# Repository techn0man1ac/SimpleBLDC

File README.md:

# SimpleBLDC

This is simple Arduino based 650W BLDC motor(with Hall sensors) controller. Designed with [KiCAD](https://www.kicad.org/). This controller has version V0.1, which means it is still under development. In addition, the project supports Field-Oriented Control (FOC), which is implemented using the [SimpleFOC library](https://github.com/simplefoc). 

All of this together enables a wide range of functions, such as precise rotor positioning (servo mode), phase current control, speed control, and much, much more. **Source code files (HW or SW) may change over time.**

Simple BLDC 3-Phase BLDC motor driver specs:
- Battery: 8S 
- VCC: 24.0V to 33.6V
- I(max): 20A 
- Сurrent measurements per phase

The device has the following features:
- XT60 power connector;
- Arduino Nano V3.0 main controller;
- Overcurrent protection (fuse);
- Reverse polarity protection;
- The ability to work with non-collector motors via Hall sensors (electric scooter or electric bicycle);
- Monitoring and control of the current of each phase (current is measured in both positive and negative directions);
- Current control by PWM, operating frequency 16/32 kHz;
- Has a connector for connecting a traction control potentiometer and a reverse button.
- Publication of the project under the [MIT license](https://github.com/techn0man1ac/SimpleBLDC/blob/main/LICENSE).

# Schematic

The device has 3 drivers for mosfet transistors, as well as 3 current sensors based on the Hall effect, which measure both in the positive and negative directions. The use of 3 sensors is the reason for the development of the device for regenerative braking.

# PCB

The board consists of two layers: top and bottom. All the main parts are located on the top layer.

The bottom layer contains mainly earth and power tracks.

Board sizes is 72 x 99 mm:

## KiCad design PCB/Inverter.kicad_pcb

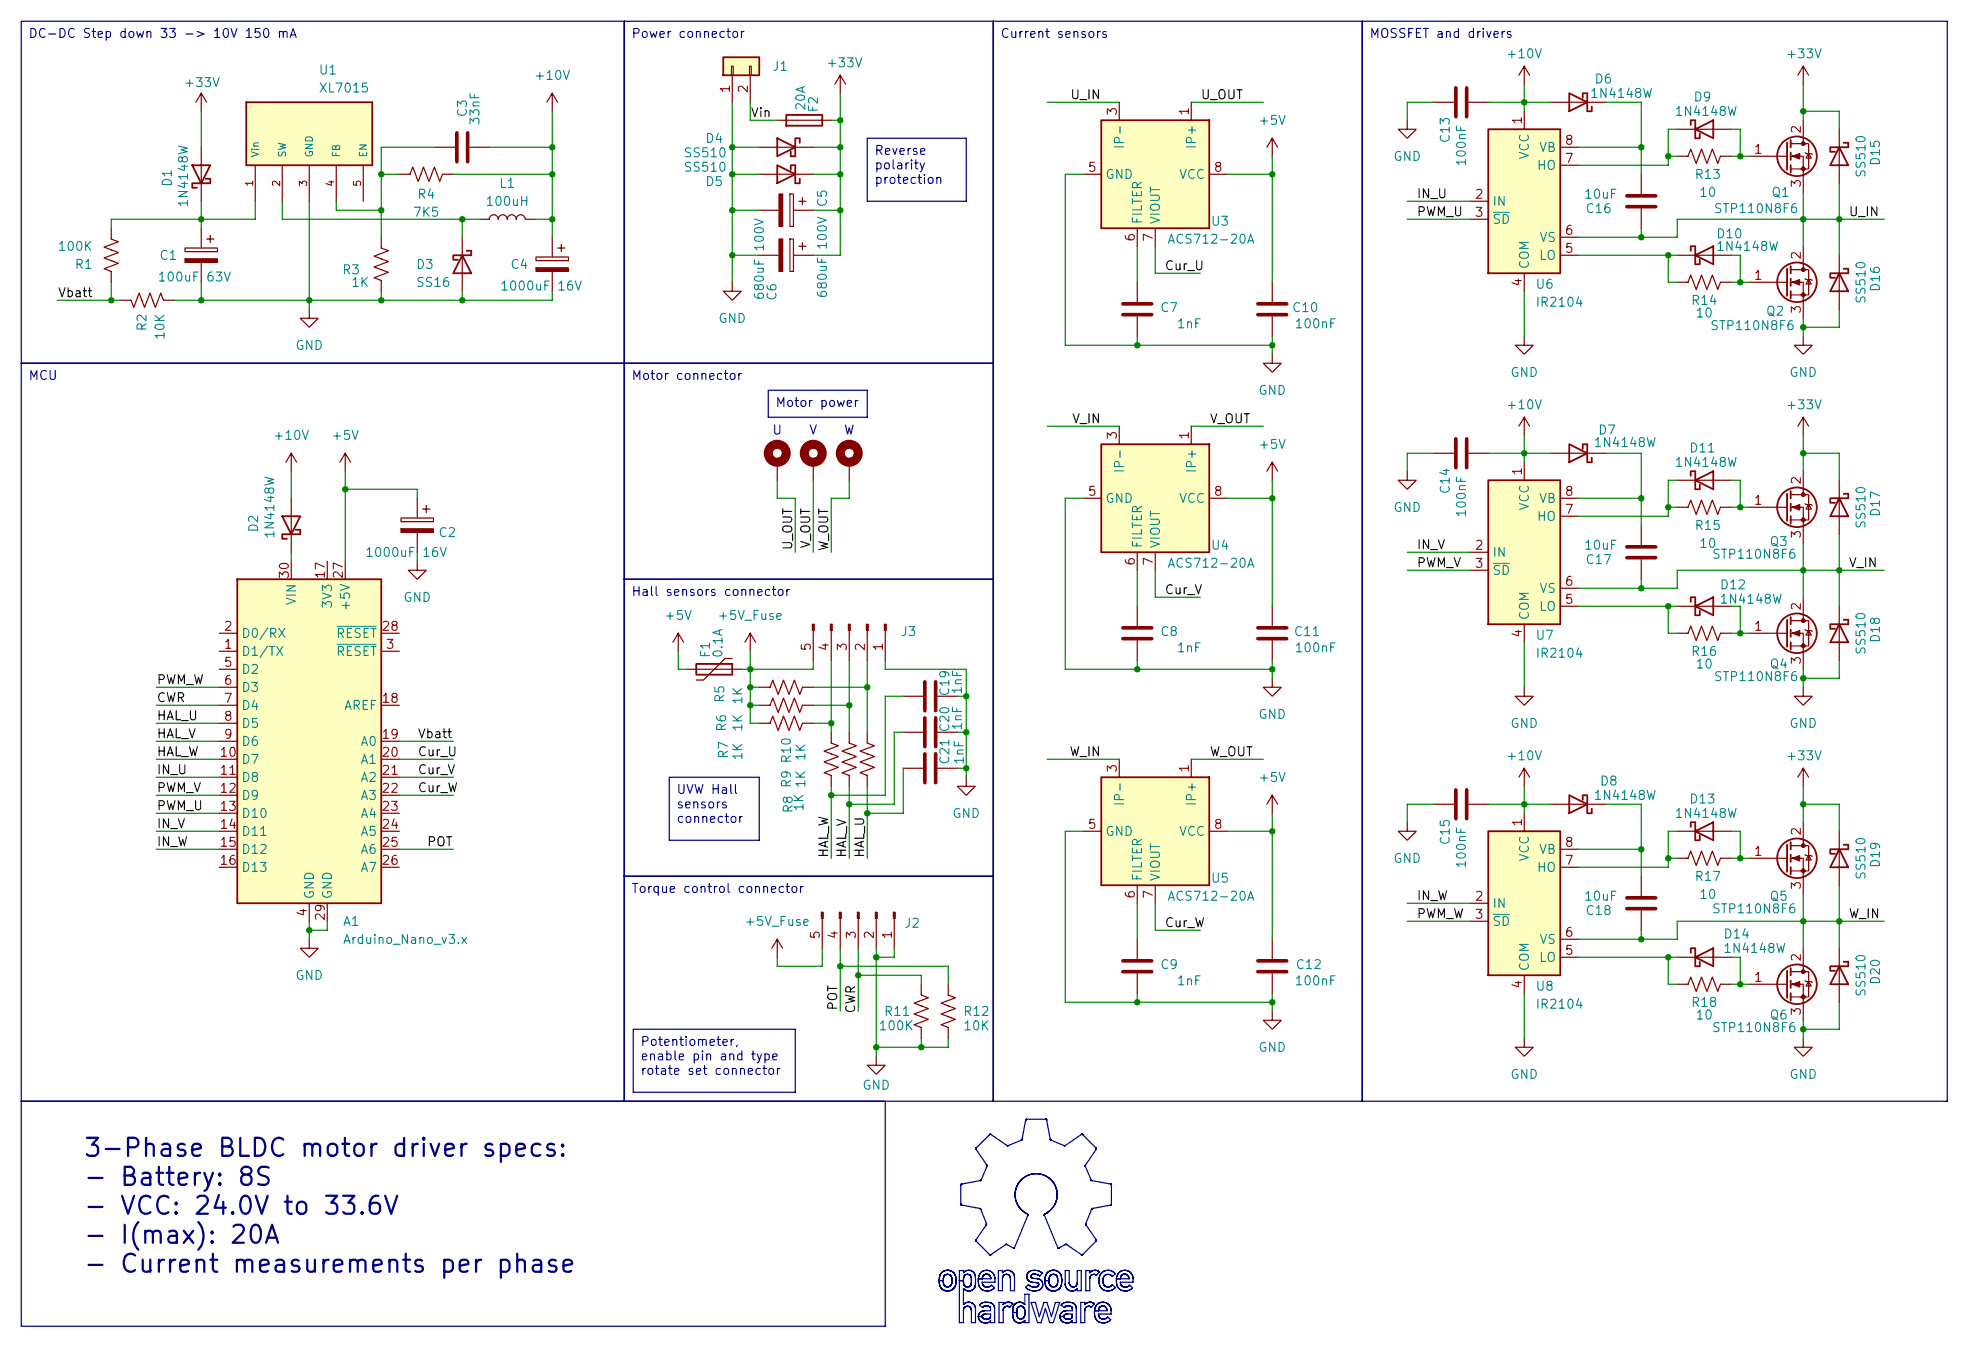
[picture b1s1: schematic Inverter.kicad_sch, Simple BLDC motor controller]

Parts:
A1: Arduino_Nano_v3.x; Arduino_Nano
C1: 100uF 63V; CP_Elec_10x10.5
C2, C4: 1000uF 16V; CP_Elec_10x10.5
C3: 33nF; C_0805_2012Metric_Pad1.18x1.45mm_HandSolder
C5, C6: 680uF 100V; CP_Radial_D16.0mm_P7.50mm
C7, C8, C9, C19, C20, C21: 1nF; C_0805_2012Metric_Pad1.18x1.45mm_HandSolder
C10, C11, C12, C13, C14, C15: 100nF; C_0805_2012Metric_Pad1.18x1.45mm_HandSolder
C16, C17, C18: 10uF; C_0805_2012Metric_Pad1.18x1.45mm_HandSolder
D1, D2, D6, D7, D8, D9, D10, D11, D12, D13, D14: 1N4148W; Nexperia_CFP3_SOD-123W
D3: SS16; D_SMA_Handsoldering
D4, D5, D15, D16, D17, D18, D19, D20: SS510; ST_D_SMC
F1: 0.1A; Fuse_1206_3216Metric
F2: 20A; FUSE_3522-2
J1: Conn_01x02; AMASS_XT60-M_1x02_P7.20mm_Vertical
J2, J3: Conn_01x05_Pin; JST_XH_B5B-XH-A_1x05_P2.50mm_Vertical
L1: 100uH; L_10.4x10.4_H4.8
Q1, Q2, Q3, Q4, Q5, Q6: STP110N8F6; TO-220-3_Horizontal_TabUp
R1, R11: 100K; R_0805_2012Metric_Pad1.20x1.40mm_HandSolder
R2, R12: 10K; R_0805_2012Metric_Pad1.20x1.40mm_HandSolder
R3, R5, R6, R7, R8, R9, R10: 1K; R_0805_2012Metric_Pad1.20x1.40mm_HandSolder
R4: 7K5; R_0805_2012Metric_Pad1.20x1.40mm_HandSolder
R13, R14, R15, R16, R17, R18: 10; R_0805_2012Metric_Pad1.20x1.40mm_HandSolder
U1: XL7015; TO-252-5_TabPin3
U2: MountingHole_Pad; MountingHole_2.2mm_M2_Pad
U3, U4, U5: ACS712-20A; SOIC-8_3.9x4.9mm_P1.27mm
U6, U7, U8: IR2104; SOIC-8_3.9x4.9mm_P1.27mm
V1: MountingHole_Pad; MountingHole_2.2mm_M2_Pad
W1: MountingHole_Pad; MountingHole_2.2mm_M2_Pad

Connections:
+5V: A1.27 (+5V), C2.1, C10.1, C11.1, C12.1, F1.2, U3.8 (VCC), U4.8 (VCC), U5.8 (VCC)
+5V_Fuse: F1.1, J2.5, J3.5, R5.2, R6.2, R7.2
+10V: C3.2, C4.1, C13.2, C14.2, C15.2, D2.2 (A), D6.2 (A), D7.2 (A), D8.2 (A), L1.2, R4.1, U6.1 (VCC), U7.1 (VCC), U8.1 (VCC)
+33V: C5.1, C6.1, D1.2 (A), D4.1 (K), D5.1 (K), D15.1 (K), D17.1 (K), D19.1 (K), F2.1, Q1.2 (D), Q3.2 (D), Q5.2 (D)
/CWR: A1.7 (D4), J2.3, R11.2
/Cur_U: A1.20 (A1), U3.7 (VIOUT)
/Cur_V: A1.21 (A2), U4.7 (VIOUT)
/Cur_W: A1.22 (A3), U5.7 (VIOUT)
/HAL_U: A1.8 (D5), C21.1, R10.1
/HAL_V: A1.9 (D6), C20.1, R9.1
/HAL_W: A1.10 (D7), C19.1, R8.1
/IN_U: A1.11 (D8), U6.2 (IN)
/IN_V: A1.14 (D11), U7.2 (IN)
/IN_W: A1.15 (D12), U8.2 (IN)
/POT: A1.25 (A6), J2.4, R12.2
/PWM_U: A1.13 (D10), U6.3 (~SD)
/PWM_V: A1.12 (D9), U7.3 (~SD)
/PWM_W: A1.6 (D3), U8.3 (~SD)
/U_IN: C16.1, D15.2 (A), D16.1 (K), Q1.3 (S), Q2.2 (D), U3.3 (IP-), U3.4 (IP-), U6.6 (VS)
/U_OUT: U2.1, U3.1 (IP+), U3.2 (IP+)
/V_IN: C17.1, D17.2 (A), D18.1 (K), Q3.3 (S), Q4.2 (D), U4.3 (IP-), U4.4 (IP-), U7.6 (VS)
/V_OUT: U4.1 (IP+), U4.2 (IP+), V1.1
/Vbatt: A1.19 (A0), R1.2, R2.2
/Vin: F2.2, J1.2
/W_IN: C18.1, D19.2 (A), D20.1 (K), Q5.3 (S), Q6.2 (D), U5.3 (IP-), U5.4 (IP-), U8.6 (VS)
/W_OUT: U5.1 (IP+), U5.2 (IP+), W1.1
GND: A1.4 (GND), A1.29 (GND), C1.2, C2.2, C4.2, C5.2, C6.2, C7.2, C8.2, C9.2, C10.2, C11.2, C12.2, C13.1, C14.1, C15.1, C19.2, C20.2, C21.2, D3.2 (A), D4.2 (A), D5.2 (A), D16.2 (A), D18.2 (A), D20.2 (A), J1.1, J2.1, J2.2, J3.1, Q2.3 (S), Q4.3 (S), Q6.3 (S), R2.1, R3.1, R11.1, R12.1, U1.3 (GND), U3.5 (GND), U4.5 (GND), U5.5 (GND), U6.4 (COM), U7.4 (COM), U8.4 (COM)
unnamed: A1.30 (VIN), D2.1 (K)
unnamed: C1.1, D1.1 (K), R1.1, U1.1 (Vin)
unnamed: D3.1 (K), L1.1, U1.2 (SW)
unnamed: C16.2, D6.1 (K), U6.8 (VB)
unnamed: C17.2, D7.1 (K), U7.8 (VB)
unnamed: C18.2, D8.1 (K), U8.8 (VB)
unnamed: D9.2 (A), Q1.1 (G), R13.1
unnamed: D9.1 (K), R13.2, U6.7 (HO)
unnamed: D10.2 (A), Q2.1 (G), R14.1
unnamed: D10.1 (K), R14.2, U6.5 (LO)
unnamed: D11.2 (A), Q3.1 (G), R15.1
unnamed: D11.1 (K), R15.2, U7.7 (HO)
unnamed: D12.2 (A), Q4.1 (G), R16.1
unnamed: D12.1 (K), R16.2, U7.5 (LO)
unnamed: D13.2 (A), Q5.1 (G), R17.1
unnamed: D13.1 (K), R17.2, U8.7 (HO)
unnamed: D14.2 (A), Q6.1 (G), R18.1
unnamed: D14.1 (K), R18.2, U8.5 (LO)
unnamed: J3.2, R5.1, R10.2
unnamed: J3.3, R6.1, R9.2
unnamed: J3.4, R7.1, R8.2
unnamed: C3.1, R3.2, R4.2, U1.4 (FB)
unnamed: C7.1, U3.6 (FILTER)
unnamed: C8.1, U4.6 (FILTER)
unnamed: C9.1, U5.6 (FILTER)

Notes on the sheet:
Power connector
3-Phase BLDC motor driver specs: - Battery: 8S - VCC: 24.0V to 33.6V - I(max): 20A - Сurrent measurements per phase
Reverse polarity protection
Current sensors
MOSSFET and drivers
Motor connector
UVW Hall sensors connector
Hall sensors connector
Motor power
MCU
DC-DC Step down 33 -> 10V 150 mA
Torque control connector
Potentiometer, enable pin and type rotate set connector

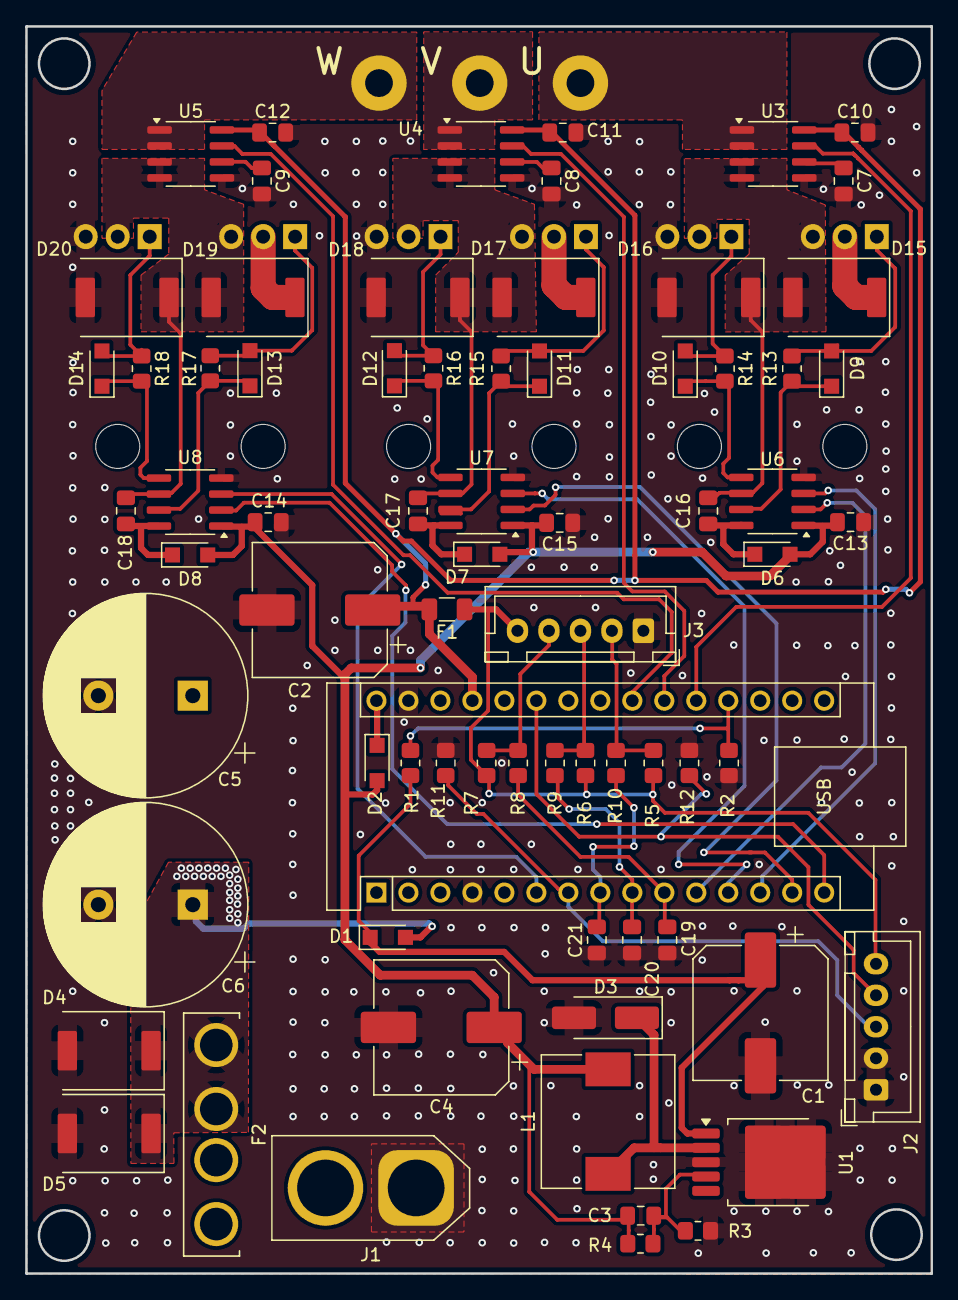
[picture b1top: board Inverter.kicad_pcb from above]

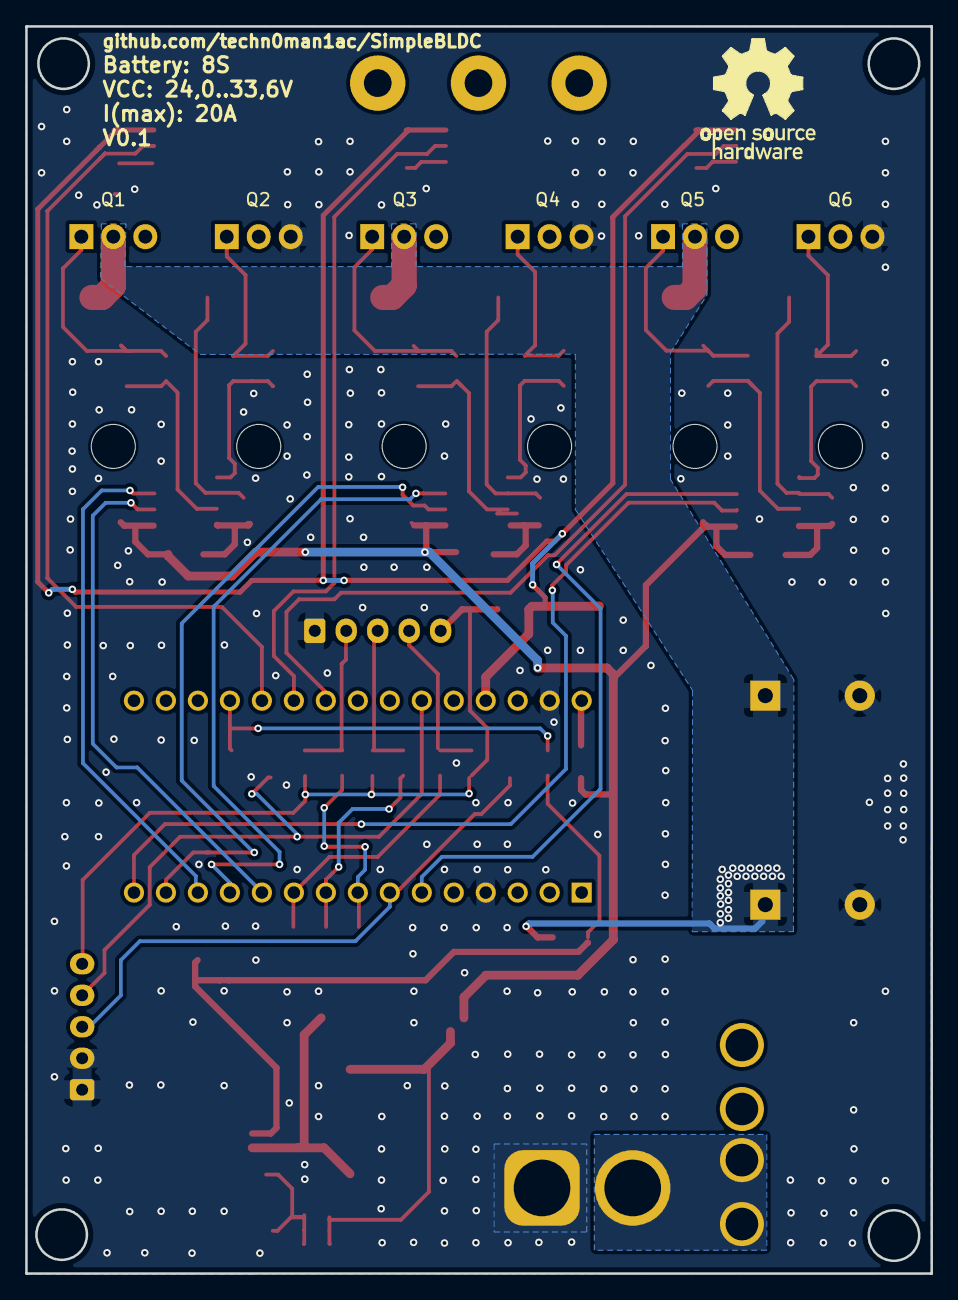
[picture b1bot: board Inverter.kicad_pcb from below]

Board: 2 copper layers, 71.9 x 99.1 mm, 82 parts (6 on the bottom side), 52 nets.

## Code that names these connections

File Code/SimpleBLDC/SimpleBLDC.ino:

/*

    This is simple Arduino based 650W BLDC motor(with Hall sensors) controller.
    https://github.com/techn0man1ac/SimpleBLDC

*/

#include <SimpleFOC.h> // https://docs.simplefoc.com/

#define PWM_U 10
#define PWM_V 9
#define PWM_W 3
#define IN_U 8
#define IN_V 11
#define IN_W 12
#define HAL_U 5
#define HAL_V 6
#define HAL_W 7
#define Vbatt A0

// BLDC motor & driver instance
// BLDCMotor motor = BLDCMotor(pole pair number);
BLDCMotor motor = BLDCMotor(15, 0.4, 20.0);
// BLDC driver instance
BLDCDriver3PWM driver = BLDCDriver3PWM(PWM_U, PWM_V, PWM_W, IN_U, IN_V, IN_W);

// Hall sensor instance
// HallSensor(int hallA, int hallB , int cpr, int index)
//  - hallA, hallB, hallC    - HallSensor A, B and C pins
//  - pp                     - pole pairs
HallSensor sensor = HallSensor(HAL_U, HAL_V, HAL_W, 15);

// velocity set point variable
float target_velocity = 0;
// instantiate the commander
Commander command = Commander(Serial);

void doTarget(char* cmd) {
  command.scalar(&target_velocity, cmd);
}

void doLimit(char* cmd) {
  command.scalar(&motor.voltage_limit, cmd);
}

ISR (PCINT2_vect) {
  sensor.update();
}

void setup() {

  // use monitoring with serial
  Serial.begin(115200);
  // enable more verbose output for debugging
  // comment out if not needed
  SimpleFOCDebug::enable(&Serial);

  pinMode(HAL_U, INPUT);
  pinMode(HAL_V, INPUT);
  pinMode(HAL_W, INPUT);

  // Using Arduino Interrupts https://dronebotworkshop.com/interrupts/
  // Enable PCIE2 Bit2 = 1 (Port D)
  PCICR |= B00000100;
  // Select PCINT21, PCINT22, PCINT23 = 1 (Pin D5, D6, D7)
  PCMSK2 |= B11100000;

  // initialize sensor sensor hardware
  sensor.init();

  // link the motor to the sensor
  motor.linkSensor(&sensor);

  // driver config
  // pwm frequency to be used [Hz]
  // for atmega328 fixed to 32kHz
  // esp32/stm32/teensy configurable
  driver.pwm_frequency = 32000;
  // power supply voltage [V]
  driver.voltage_power_supply = getBatteryVoltage();
  driver.init();
  // link the motor and the driver
  motor.linkDriver(&driver);

  // aligning voltage [V]
  motor.voltage_sensor_align = 3;

  // set motion control loop to be used
  motor.controller = MotionControlType::velocity;

  // contoller configuration
  // default parameters in defaults.h

  // velocity PI controller parameters
  motor.PID_velocity.P = 0.2f;
  motor.PID_velocity.I = 2;
  motor.PID_velocity.D = 0;
  // default voltage_power_supply
  motor.voltage_limit = 6;
  // jerk control using voltage voltage ramp
  // default value is 300 volts per sec  ~ 0.3V per millisecond
  motor.PID_velocity.output_ramp = 1000;

  // velocity low pass filtering time constant
  motor.LPF_velocity.Tf = 0.01f;

  // comment out if not needed
  motor.useMonitoring(Serial);

  // initialize motor
  motor.init();
  // align sensor and start FOC
  motor.initFOC();

  // add target command T
  command.add('T', doTarget, "target voltage");
  command.add('L', doLimit, "voltage limit");

  Serial.println(F("Motor ready."));
  Serial.println(F("Set the target velocity using serial terminal:"));
  _delay(1000);
}


void loop() {
  // main FOC algorithm function
  // the faster you run this function the better
  // Arduino UNO loop  ~1kHz
  // Bluepill loop ~10kHz
  motor.loopFOC();
  float battVoltage = getBatteryVoltage();
  driver.voltage_power_supply = battVoltage;
  // Motion control function
  // velocity, position or voltage (defined in motor.controller)
  // this function can be run at much lower frequency than loopFOC() function
  // You can also use motor.move() and set the motor.target in the code
  motor.move(target_velocity);

  // function intended to be used with serial plotter to monitor motor variables
  // significantly slowing the execution down!!!!
  // motor.monitor();

  // user communication
  command.run();
  Serial.println(battVoltage, 2);
}

float getBatteryVoltage() {
  return analogRead(Vbatt) * (55.0 / 1023.0);
}

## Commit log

2025-04-06 Change#000
    Start
2025-04-06 Change#000
    Start second try
2025-04-07 Change#001
    I replaced the DC-DC converter chip with a higher voltage one, 80 V versus 40 V as before.
2025-04-07 Change#001
    Add open-source hardware logo
2025-04-07 #Change002
    Add device parameters
2025-04-07 #Change002
    Add scheme in png
2025-04-07 Change#002
    Add specs and schematic image
2025-04-09 Change#003
    Schematic changes
2025-04-09 Change#004
    Update schematics
2025-04-13 Change#005
    PCB 90%
2025-04-13 Change#005
    Cosmetics
2025-04-13 Change#006
    Add PCB gerber files.
2025-04-14 Change#007
    Add OSHW logo and PCB 3d model in step format
2025-04-14 Change#007
    Update README.md
2025-04-14 Change #007
    Update README.md
2025-04-22 Change#008
    Ready for fabrication
2025-04-22 Change#009
    Update README.md
2025-04-22 Change#009
    upd
2025-05-11 Change#009
    Changed the pin on phase W from 5 to 3 (so that all PWMs are at the same frequency);
    Added a thermal barrier for all components on the negative side to make it easier to assemble the device;
    Changed the size of the board, it became a little larger (to increase the ground current);
    Added frames for connectors with a description in the diagram for a better understanding of which connector is for what.
2025-05-11 Change#009
    Actual gerbers files
2025-05-11 Change#009
    Add Arduino code
2025-05-11 Change#009
    Add photo real device.
2025-05-11 Change#010
    Update README.md
2025-05-11 Change#010
    Update SimpleBLDC.ino
2025-05-17 Change#011
    Change hall sensor pin 13 -> 5
2025-05-17 Change#011
    Update README.md
2025-05-17 Change#011
    Add real device photos
2025-05-17 Change#011
    Update SimpleBLDC.ino
2025-05-17 Change#012
    Work code
    https://www.youtube.com/shorts/_VDWO1sNHf8
2025-05-17 Change#012
    Add new version of code, many fixes
2025-05-19 Change#013
    Add interrupt for hall sensors
2025-05-22 Change#012
    The outputs on the board for setting the operation of half-bridges have been changed, as well as the inputs for Hall sensors, so that they are in the space of one port and read by one line of code, a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
2025-05-22 Change#013
    Deleted some unused stuff
2025-05-22 Change#013
    Delete PCB/Gerbers/Gerbers.zip
2025-05-23 Change#014
    Added capacitors for the outputs from the Hall sensors.
2025-05-23 Change#014
    Delete PCB/Gerbers/Inverter_Gerbers.zip
2025-05-23 Change#014
    Add 3 filtering capacitors
2025-05-25 Change#015
    Add set PWM transistors frequency 16 kHz flag
2026-06-01 Change#016
    I have updated the source code, which uses the SimpleFOC library to implement many functions, such as precise positioning, motor speed control, motor parameter measurement, and implementation of the 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
2026-06-01 Change#17
    Update README.md
